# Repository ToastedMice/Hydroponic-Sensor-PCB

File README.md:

# Hydroponic-Sensor-PCB

A custom PCB designed for managing a smart hydroponic system. It will definitly need some modification as my use case is so specifc. It integrates components needed to automate water and nutrient delivery using peristaltic pumps and sensor feedback. I chose to use cheap sensors rather than good ones so that might need changing too.

## Features

- **5x N-Channel MOSFETs**  
  For switching 0-36v peristaltic pumps, I used NRF20L01's but it would probably be better for Rpi to get some logic level mosfets.

- **Sensor Support**  
  Has a port for pH sensor,EC, i2C USB port for a TSL2591 light sensor.

- **Microcontroller-Friendly**  
  Headers make it easy to connect additional i2c or 5v devices.

- **Compact Form Factor**  
  Layout for enclosure mounting and wire management. pH, EC, Battery could go inside a case

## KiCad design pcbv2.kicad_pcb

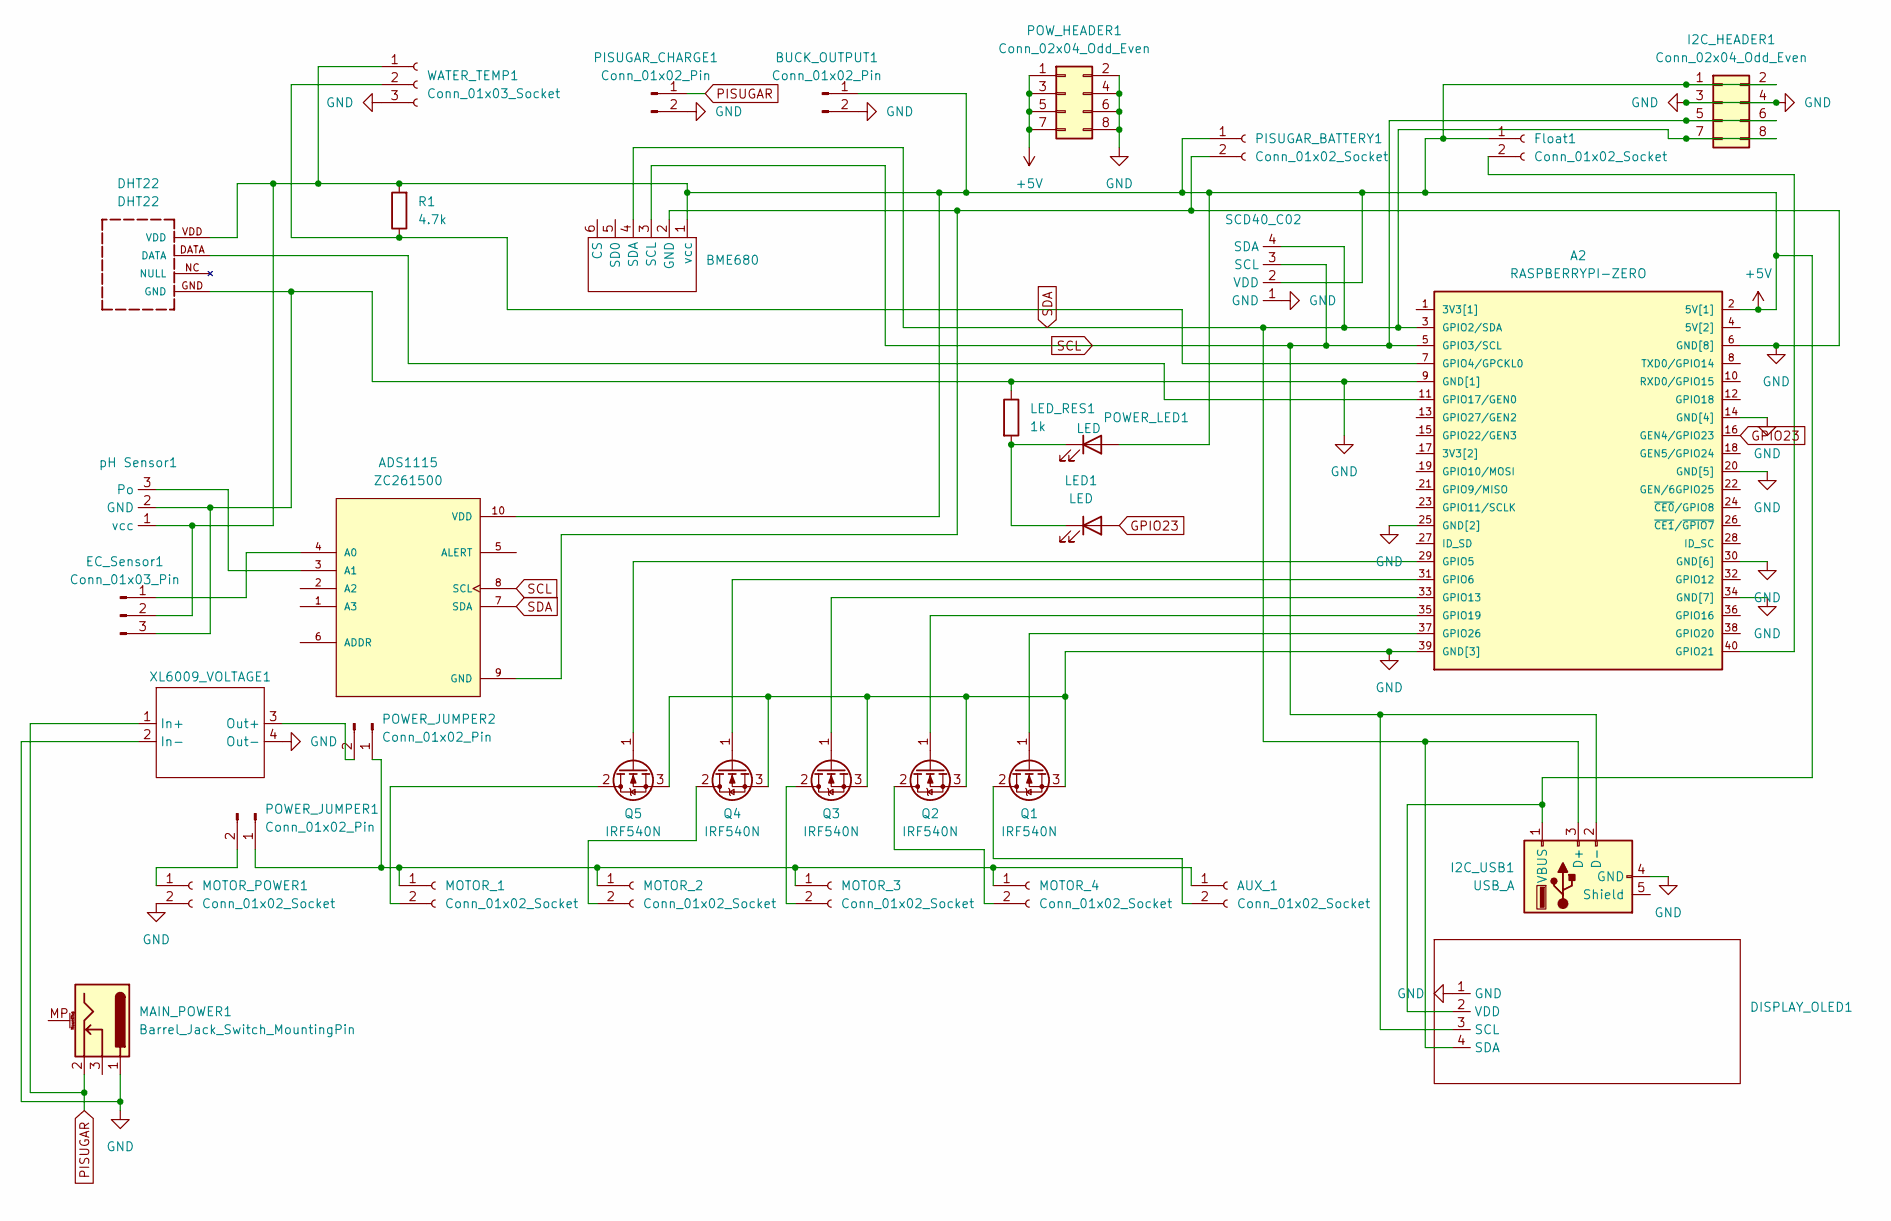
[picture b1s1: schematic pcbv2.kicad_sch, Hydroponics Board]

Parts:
A2: RASPBERRYPI-ZERO; RASPBERRYPI-ZERO_RPI-ZERO
ADS1115: ZC261500; MODULE_ZC261500; PARTREV NA
AUX_1: Conn_01x02_Socket; JST_XH_S2B-XH-A-1_1x02_P2.50mm_Horizontal
BME680: PinSocket_1x06_P2.54mm_Vertical
BUCK_OUTPUT1: Conn_01x02_Pin; JST_XH_S2B-XH-A-1_1x02_P2.50mm_Horizontal
DHT22: DHT22
DISPLAY_OLED1: JST_XH_S4B-XH-A-1_1x04_P2.50mm_Horizontal
EC_Sensor1: Conn_01x03_Pin; JST_XH_S3B-XH-A-1_1x03_P2.50mm_Horizontal
Float1: Conn_01x02_Socket; JST_XH_S2B-XH-A-1_1x02_P2.50mm_Horizontal
I2C_HEADER1: Conn_02x04_Odd_Even; PinHeader_2x04_P2.54mm_Vertical
I2C_USB1: USB_A; USB_A_Kycon_KUSBX-AS1N-B_Horizontal
LED1: LED; LED_D3.0mm
LED_RES1: 1k; R_Axial_DIN0207_L6.3mm_D2.5mm_P10.16mm_Horizontal
MAIN_POWER1: Barrel_Jack_Switch_MountingPin; BarrelJack_Horizontal
MOTOR_1, MOTOR_2, MOTOR_3, MOTOR_4: Conn_01x02_Socket; JST_XH_S2B-XH-A-1_1x02_P2.50mm_Horizontal
MOTOR_POWER1: Conn_01x02_Socket; JST_XH_S2B-XH-A-1_1x02_P2.50mm_Horizontal
PISUGAR_BATTERY1: Conn_01x02_Socket; JST_XH_S2B-XH-A-1_1x02_P2.50mm_Horizontal
PISUGAR_CHARGE1: Conn_01x02_Pin; JST_XH_S2B-XH-A-1_1x02_P2.50mm_Horizontal
POWER_JUMPER1, POWER_JUMPER2: Conn_01x02_Pin; PinHeader_1x02_P2.54mm_Vertical
POWER_LED1: LED; LED_D3.0mm
POW_HEADER1: Conn_02x04_Odd_Even; PinHeader_2x04_P2.54mm_Vertical
Q1, Q2, Q3, Q4, Q5: IRF540N; TO-220-3_Vertical
R1: 4.7k; R_Axial_DIN0207_L6.3mm_D2.5mm_P10.16mm_Horizontal
SCD40_C02: PinSocket_1x04_P2.54mm_Vertical
WATER_TEMP1: Conn_01x03_Socket; JST_XH_S3B-XH-A-1_1x03_P2.50mm_Horizontal
XL6009_VOLTAGE1: XL6009
pH Sensor1: JST_XH_S3B-XH-A-1_1x03_P2.50mm_Horizontal

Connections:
+5V: A2.2 (5V[1]), ADS1115.10 (VDD), BME680.1 (vcc), BUCK_OUTPUT1.1, DHT22.VDD, DISPLAY_OLED1.2 (VDD), EC_Sensor1.2, Float1.1, I2C_HEADER1.1, I2C_HEADER1.2, I2C_USB1.1 (VBUS), PISUGAR_BATTERY1.1, POWER_LED1.2 (A), POW_HEADER1.1, POW_HEADER1.3, POW_HEADER1.5, POW_HEADER1.7, R1.2, SCD40_C02.2 (VDD), WATER_TEMP1.1, pH Sensor1.1 (vcc)
GND: A2.6 (GND[8]), A2.9 (GND[1]), A2.14 (GND[4]), A2.20 (GND[5]), A2.25 (GND[2]), A2.30 (GND[6]), A2.34 (GND[7]), A2.39 (GND[3]), ADS1115.9 (GND), BME680.2 (GND), BUCK_OUTPUT1.2, DHT22.GND, DISPLAY_OLED1.1 (GND), EC_Sensor1.3, I2C_HEADER1.3, I2C_HEADER1.4, I2C_USB1.4 (GND), LED_RES1.1, MAIN_POWER1.1, MOTOR_POWER1.2, PISUGAR_BATTERY1.2, PISUGAR_CHARGE1.2, POW_HEADER1.2, POW_HEADER1.4, POW_HEADER1.6, POW_HEADER1.8, Q1.3 (S), Q2.3 (S), Q3.3 (S), Q4.3 (S), Q5.3 (S), SCD40_C02.1 (GND), WATER_TEMP1.3, XL6009_VOLTAGE1.2 (In-), XL6009_VOLTAGE1.4 (Out-), pH Sensor1.2 (GND)
GPIO23: A2.16 (GEN4/GPIO23), LED1.2 (A)
unnamed: A2.7 (GPIO4/GPCKL0), R1.1, WATER_TEMP1.2
unnamed: A2.29 (GPIO5), Q5.1 (G)
unnamed: A2.31 (GPIO6), Q4.1 (G)
unnamed: A2.33 (GPIO13), Q3.1 (G)
unnamed: A2.11 (GPIO17/GEN0), DHT22.DATA
unnamed: A2.35 (GPIO19), Q2.1 (G)
unnamed: A2.40 (GPIO21), Float1.2
unnamed: A2.37 (GPIO26), Q1.1 (G)
unnamed: ADS1115.4 (A0), EC_Sensor1.1
unnamed: ADS1115.3 (A1), pH Sensor1.3 (Po)
unnamed: AUX_1.1, MOTOR_1.1, MOTOR_2.1, MOTOR_3.1, MOTOR_4.1, POWER_JUMPER1.1, POWER_JUMPER2.1
unnamed: AUX_1.2, Q1.2 (D)
unnamed: LED1.1 (K), LED_RES1.2, POWER_LED1.1 (K)
unnamed: MOTOR_1.2, Q5.2 (D)
unnamed: MOTOR_2.2, Q4.2 (D)
unnamed: MOTOR_3.2, Q3.2 (D)
unnamed: MOTOR_4.2, Q2.2 (D)
unnamed: MOTOR_POWER1.1, POWER_JUMPER1.2
unnamed: POWER_JUMPER2.2, XL6009_VOLTAGE1.3 (Out+)
PISUGAR: MAIN_POWER1.2, PISUGAR_CHARGE1.1, XL6009_VOLTAGE1.1 (In+)
SCL: A2.5 (GPIO3/SCL), ADS1115.8 (SCL), BME680.3 (SCL), DISPLAY_OLED1.3 (SCL), I2C_HEADER1.5, I2C_HEADER1.6, I2C_USB1.2 (D-), SCD40_C02.3 (SCL)
SDA: A2.3 (GPIO2/SDA), ADS1115.7 (SDA), BME680.4 (SDA), DISPLAY_OLED1.4 (SDA), I2C_HEADER1.7, I2C_HEADER1.8, I2C_USB1.3 (D+), SCD40_C02.4 (SDA)

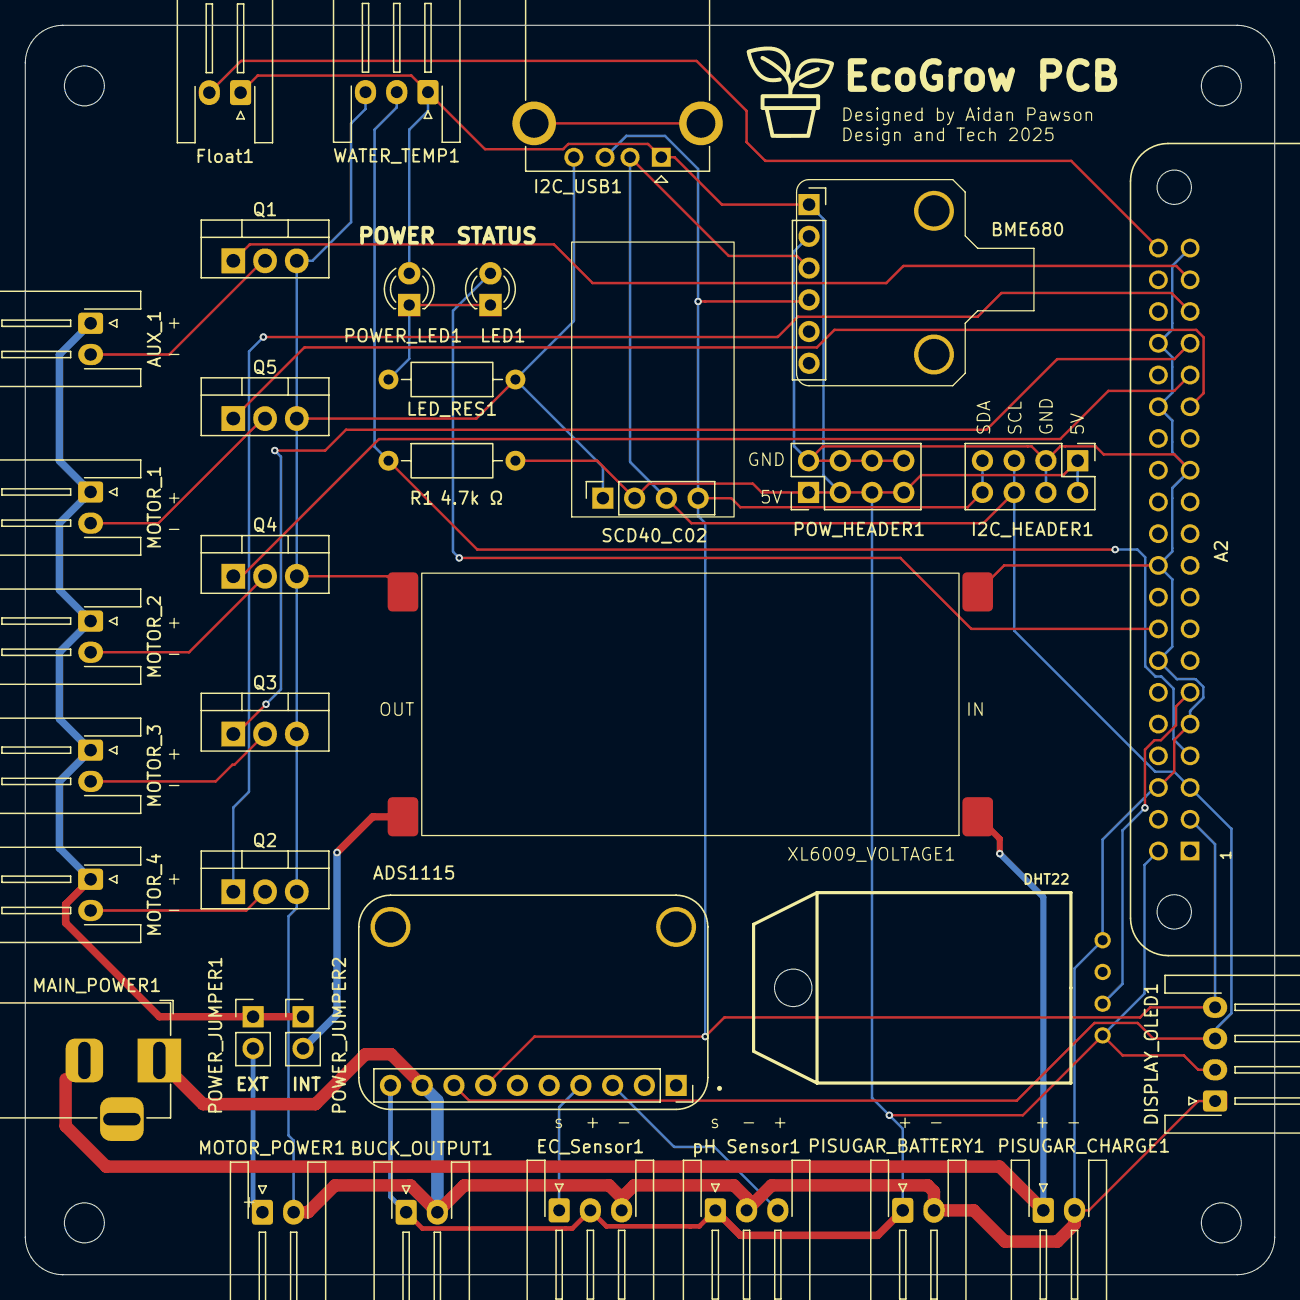
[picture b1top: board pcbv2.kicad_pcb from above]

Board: 2 copper layers, 100.0 x 100.0 mm, 40 parts (1 on the bottom side), 25 nets.

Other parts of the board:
GDead_Plant: LOGO
M3_3.2mm_1, M3_3.2mm_2, M3_3.2mm_3, M3_3.2mm_4: MountingHole_3.2mm_M3
